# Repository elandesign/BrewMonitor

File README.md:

# Brew Monitor

An attempt to build a WiFi connected hydrometer & temperature monitor

## Theory

As wort ferments, the specific gravity (i.e. density relative to water) falls. Using Archimedes’ principle we can determine the SG at any given time by suspending a weight of known volume and mass in the fermenting wort.

_The following working assumes a density of 1g/cc of pure water under ideal conditions._

> A weight of volume 100cc and 150g mass is submersed in pure water. The upwards force is equal to the volume of displaced water (100g), giving the weight a net mass of 50g.
> 
> The same weight submersed in wort at 1.050 SG would displace 105g of wort giving the weight a net mass of 45g.
> 
> Measuring the change in force imparted by the weight over time will allow us to accurately monitor the fermentation process.
> 
> Corrections can be applied to account for temperature and atmospheric pressure if needed.

## Design

At its simplest, the brew monitor should consist of a weight attached to a load cell. The weight should be of a known volume and mass (we can ignore the mass and volume of the cord suspending the weight as negligible)

The weight must have a greater density than that of the wort in order to sink, so I’ll aim for 1.2g/cc (1.200) which should be more than enough for even the strongest brews.

## Prototype Bill of Materials (all from eBay)

* 6cm plastic sphere
* Stainless steel wire
* 100g Load Cell
* HX711 Load Cell ADC
* ESP-03 ESP8266 Module
* BMP180 Temperature/Pressure Sensor
* 128x64 OLED Display
* 3.3V Regulator
* Reset Switch
* Power Socket
* Circuit Board (Eagle files tbc)
* Enclosure
* PSU

## Software Plan

### Initialization:

* Check reset switch state
  * Holding reset for n seconds when applying power clears filesystem settings
* Load settings from filesystem
  * If wifi settings are present, attempt to connect to wifi
  * If not start in AP mode to allow initial configuration

### Run Mode:

* Accept http GETs to /status.json - return JSON temperature/weight/pressure/sg readings
* Accept http POSTs to /configure - write settings to filesystem
* Accept http GETs to /settings - read current config from filesystem
* Periodically send JSON status to external server if configured
* Tare - press reset switch for n seconds to update tare reading in filesystem settings

### OTA Updates:

* It should be possible to update the firmware over the internet

## Unknowns & Problem Areas

* We need to accurately measure the volume of the weight
* Do we need to calibrate the load cell?
* How can we account for CO2 bubbles adhering to the surface of the weight? Will the effect be significant?
* Does the density of wort due to temperature and pressure change in line with that of pure water?
* Ideally we’d take the temperature of the wort - will ambient temperature be good enough to get reasonable accuracy?
* How do we enclose the thing? An off the shelf project box would be best to keep price down, but we need to be careful not to expose the wort to infection - would need to be airtight. Also, if this is to replace the airlock we’d need a bubbler/blowoff tube as part of the setup.
* Is the weight food-safe?

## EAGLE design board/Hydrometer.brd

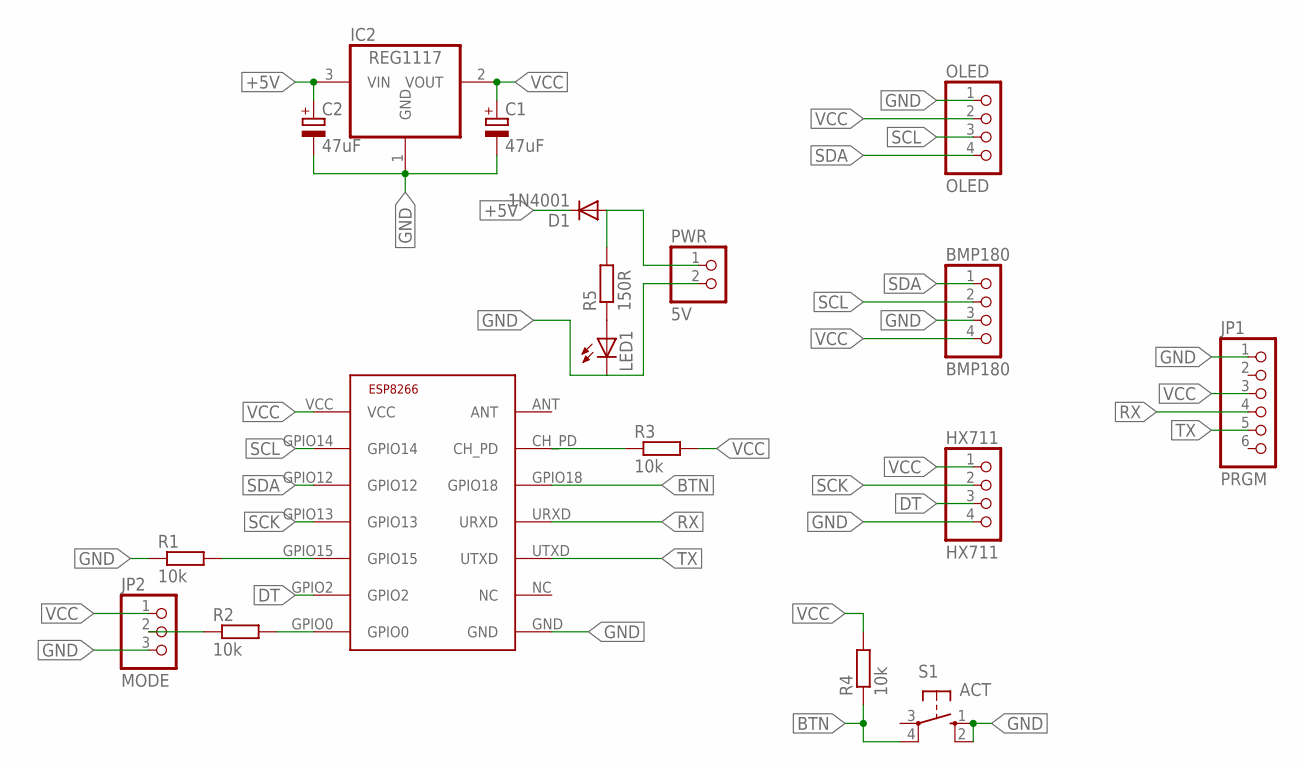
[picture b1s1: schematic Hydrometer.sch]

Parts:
BMP180: BMP180; 1X04
C1: 47uF; E2-5
C2: 47uF; E2,5-5
D1: 1N4001; DO41-10
HX711: HX711; 1X04
IC2: REG1117; SOT223
JP1: PRGM; 1X06
JP2: MODE; 1X03
LED1: LED3MM
OLED: OLED; 1X04
PWR: 5V; 1X02
R1, R3, R4: 10k; R1206
R2: 10k; 0204/7
R5: 150R; 0204/7
S1: ACT; B3F-10XX
U$1: ESP8266-03; ESP-03

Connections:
+5V: C2.+, D1.C, IC2.3 (VIN)
BTN: R4.1, S1.4 (P1), U$1.GPIO18
DT: HX711.3, U$1.GPIO2
DTR: R2.2, U$1.GPIO0
GND: BMP180.3, C1.-, C2.-, HX711.4, IC2.1 (GND), JP1.1, JP2.3, LED1.K (C), OLED.1, PWR.2, R1.1, S1.1 (S), S1.2 (S1), U$1.GND
unnamed: JP2.2, R2.1
unnamed: R1.2, U$1.GPIO15
unnamed: D1.A, PWR.1, R5.2
unnamed: R3.1, U$1.CH_PD
unnamed: LED1.A, R5.1
RX: JP1.4, U$1.URXD
SCK: HX711.2, U$1.GPIO13
SCL: BMP180.2, OLED.3, U$1.GPIO14
SDA: BMP180.1, OLED.4, U$1.GPIO12
TX: JP1.5, U$1.UTXD
VCC: BMP180.4, C1.+, HX711.1, IC2.2 (VOUT), JP1.3, JP2.1, OLED.2, R3.2, R4.2, U$1.VCC

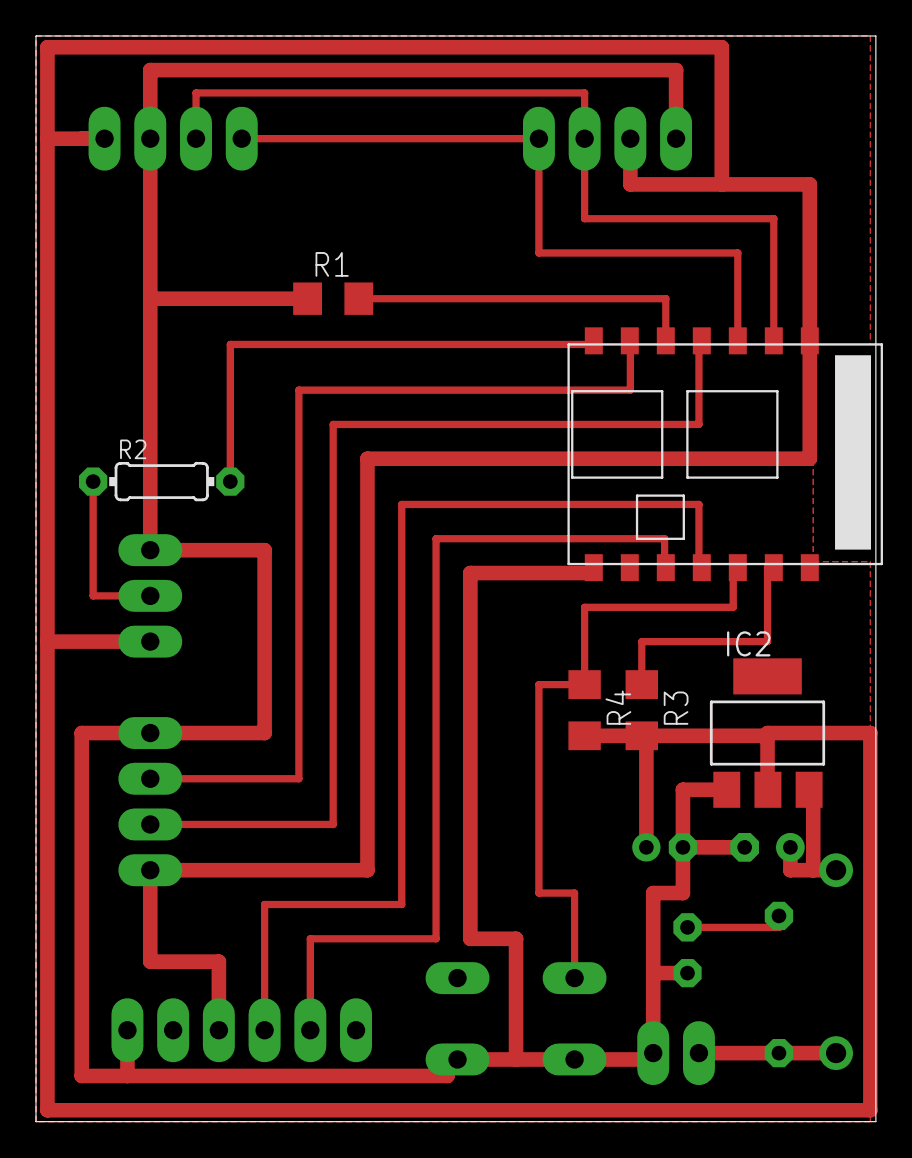
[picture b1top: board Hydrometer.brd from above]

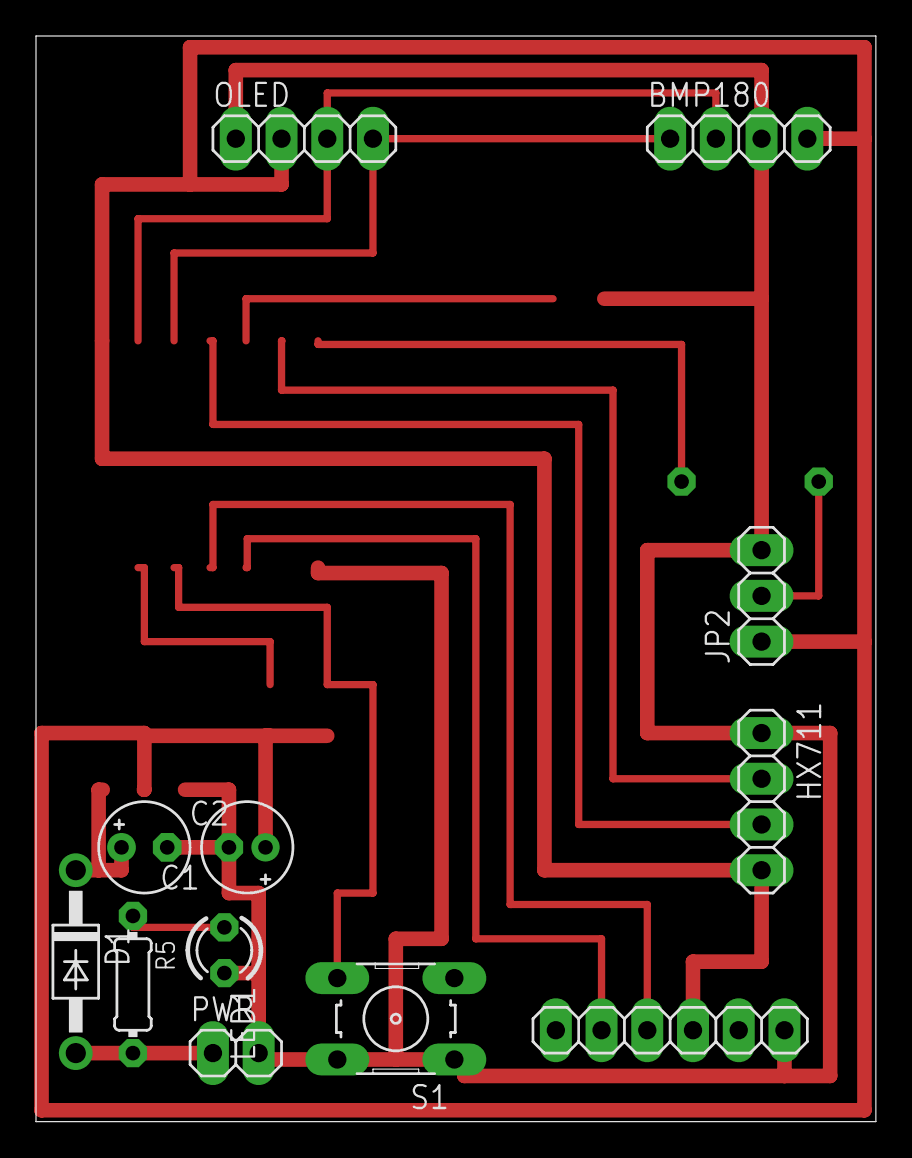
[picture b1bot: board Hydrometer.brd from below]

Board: 2 copper layers, 46.7 x 60.3 mm, 18 parts (12 on the bottom side), 16 nets.

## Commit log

2016-03-30 Initial commit.
2016-03-30 Working. Kinda
2016-03-31 Start to add web interface. File serving seems borked...
2016-03-31 Add README.md
2016-03-31 Add eagle schematic
2016-04-05 Clean up schematic and board
2016-04-15 Read the load cell along with other sensors
2016-04-15 Send readings to graphite server over UDP
2016-04-23 Switch from Makefile to platformio builds
2016-05-22 Update board layout to a (mostly) single sided PCB
2016-05-22 Switch from Makefile to PlatformIO build system
2016-05-22 Remove unused SPI code from SSD1306 library
2016-05-22 Add fill planes to board
2016-05-23 Add input protection and power LED
